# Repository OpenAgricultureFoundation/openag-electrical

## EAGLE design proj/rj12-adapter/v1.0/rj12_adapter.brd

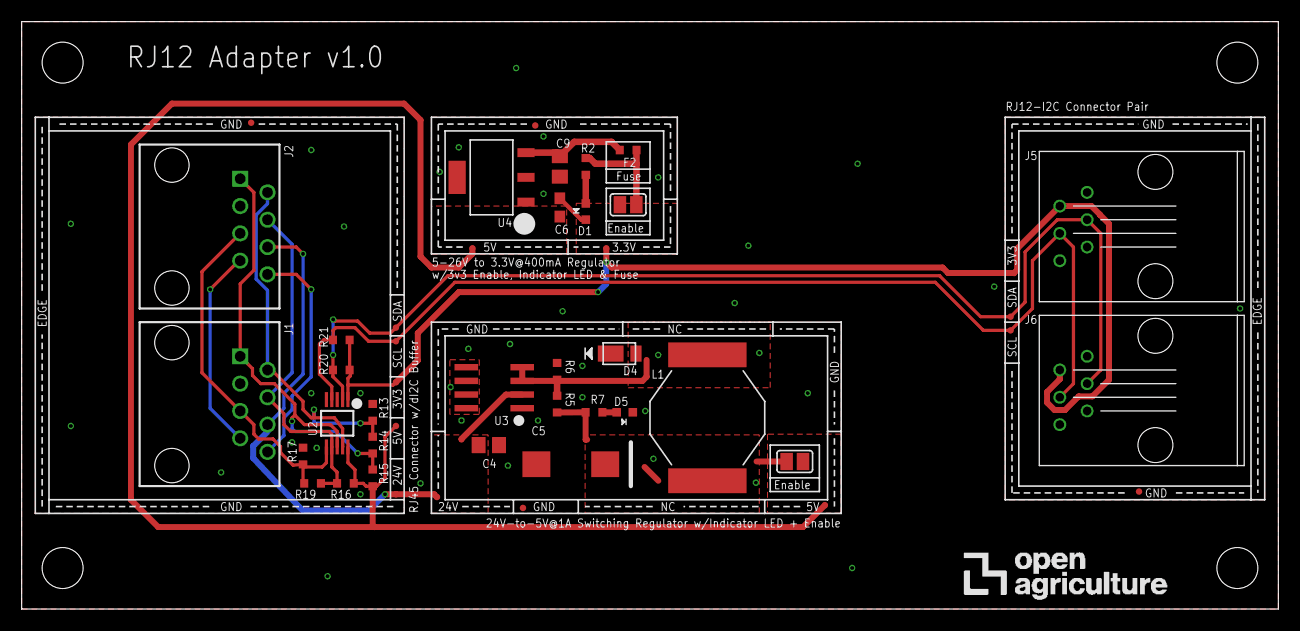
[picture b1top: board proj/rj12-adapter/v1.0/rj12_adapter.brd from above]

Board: 2 copper layers, 116.8 x 54.6 mm, 52 parts (1 on the bottom side), 18 nets.

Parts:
C4: 15uF; C0805
C5: 220uF; CT7343
C6: 0.1uF; C0603
C9: 10uF; C0805
D1, D5: APT1608; CHIPLED_0603
D4: SBR2A40P1-7; POWERDI123
F2: 400mA; 0603
FRAME1: DOCFIELD
J1, J2: 54602-908LF; OPENAG-V1-RJ45
J5, J6: OPENAG-I2C-RJ12
L1: 68uH; UP2B
R2, R7: 100; RC0603N
R5: 3.01K; RC0603N
R6: 976 Ohm; RC0603N
R13, R15, R16, R17: 600; RC0603N
R14, R19: 120; RC0603N
R20, R21: 10K; RC0603N
SJ2, SJ3: SOLDERJUMPER_REFLOW_NOPASTE
TP4, TP5, TP6, TP7, TP8, TP9, TP11, TP12, TP13, TP14, TP29, TP30, TP32, TP33, TP34, TP35: TPTP06R; TP06R
U2: PCA9615; SOP50P490X110-10N
U3: MIC4680; SOIC8
U4: LM2937; MP04A
U$1, U$2, U$3, U$4: OPENAG-CORNER-MOUNTING-HOLE
U$5: OPENAG-LOGO-750-MIL

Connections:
+3V3: J5.5, J6.5, R20.2, R21.2, SJ3.2, TP11.TP, TP30.TP, TP32.TP, U2.1
+5V: C6.1, R15.1, R16.2, SJ2.2, TP5.TP, TP29.TP, TP34.TP, U2.10, U4.1
+24V: C4.1, J1.24V(6), J2.24V(6), TP7.TP, TP35.TP, U3.2
DSCLM: J1.DSCLM(5), J2.DSCLM(5), R17.2, R19.1, U2.6
DSCLP: J1.DSCLP(4), J2.DSCLP(4), R16.1, R19.2, U2.7
DSDAM: J1.DSDAM(2), J2.DSDAM(2), R13.1, R14.2, U2.9
DSDAP: J1.DSDAP(1), J2.DSDAP(1), R14.1, R15.2, U2.8
GND: C4.2, C5.-, C6.2, C9.2, D1.C, D4.-, D5.C, J1.GND(3), J2.GND(3), J5.1, J6.1, R6.1, R13.2, R17.1, TP4.TP, TP6.TP, TP13.TP, TP33.TP, U2.5, U3.1, U3.5, U3.6, U3.7, U3.8, U4.2, U4.4
unnamed: D1.A, R2.1
unnamed: C9.1, F2.1, U4.3
unnamed: D4.+, L1.1, R5.1, R6.2, U3.3, U3.4
unnamed: D5.A, R7.1
unnamed: C5.+, L1.2, R5.2, R7.2, SJ2.1
REG_3V3_400MA: F2.2, R2.2, SJ3.1
SCL: J5.3, J6.3, R21.1, TP8.TP, TP12.TP, U2.4
SDA: J5.4, J6.4, R20.1, TP9.TP, TP14.TP, U2.2
USBM: J1.USBM(8), J2.USBM(8)
USBP: J1.USBP(7), J2.USBP(7)

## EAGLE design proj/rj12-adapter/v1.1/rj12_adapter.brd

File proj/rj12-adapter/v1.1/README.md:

# RJ12 to RJ45 Adapter v1.1
Enables devices on RJ12-I2C comm
system to interface with RJ45-dI2C-USB
comm system. Converts 24V & dI2C on 
RJ45 to 3V3 & I2C on RJ12.

### Contents
1. [Schematic](#schematic)
2. [Board Top](#board-top)
3. [Board Bottom](#board-bottom)
4. [Bill of Materials](rj12_adapter.csv)
5. [Gerber Files](rj12_adapter_v_1_1.zip)

### Schematic

### Board Top

### Board Bottom

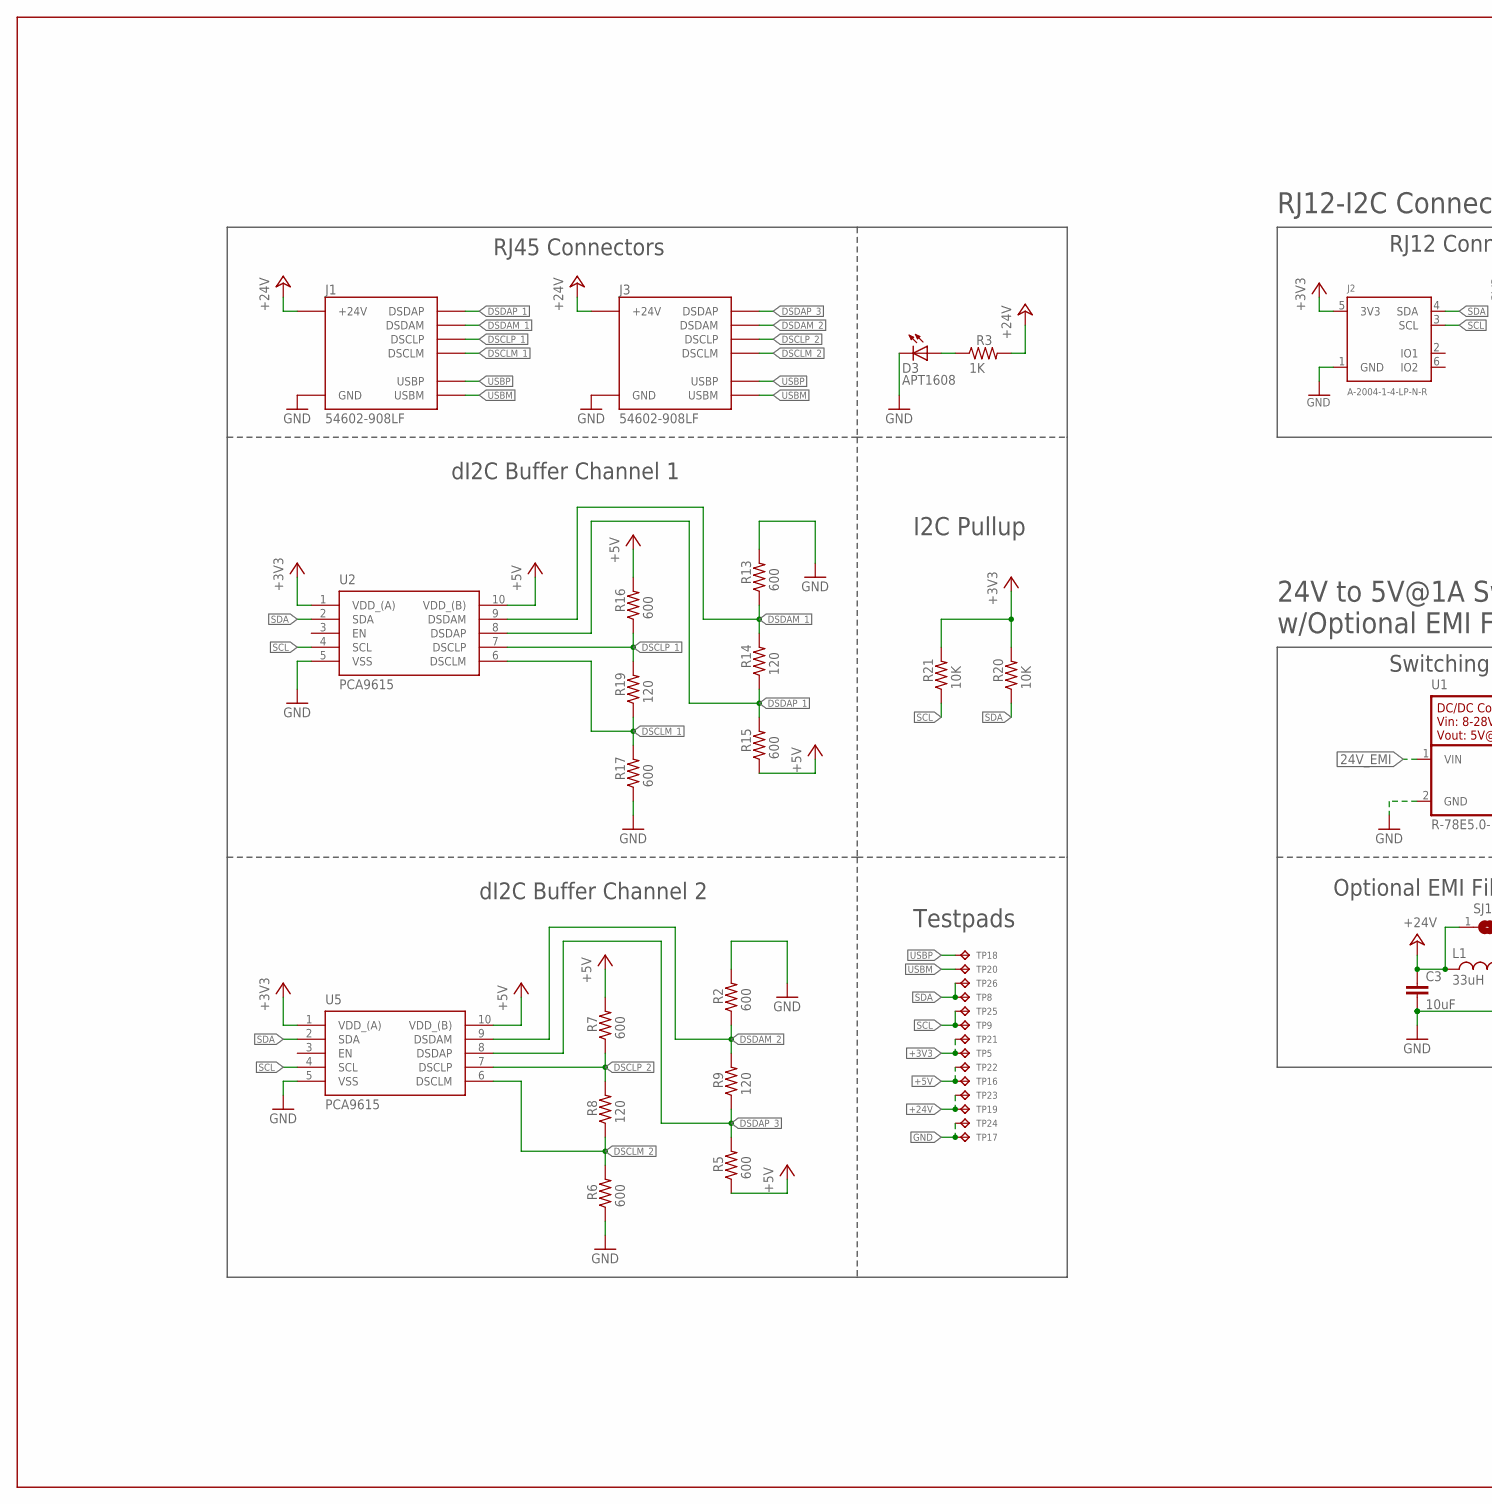
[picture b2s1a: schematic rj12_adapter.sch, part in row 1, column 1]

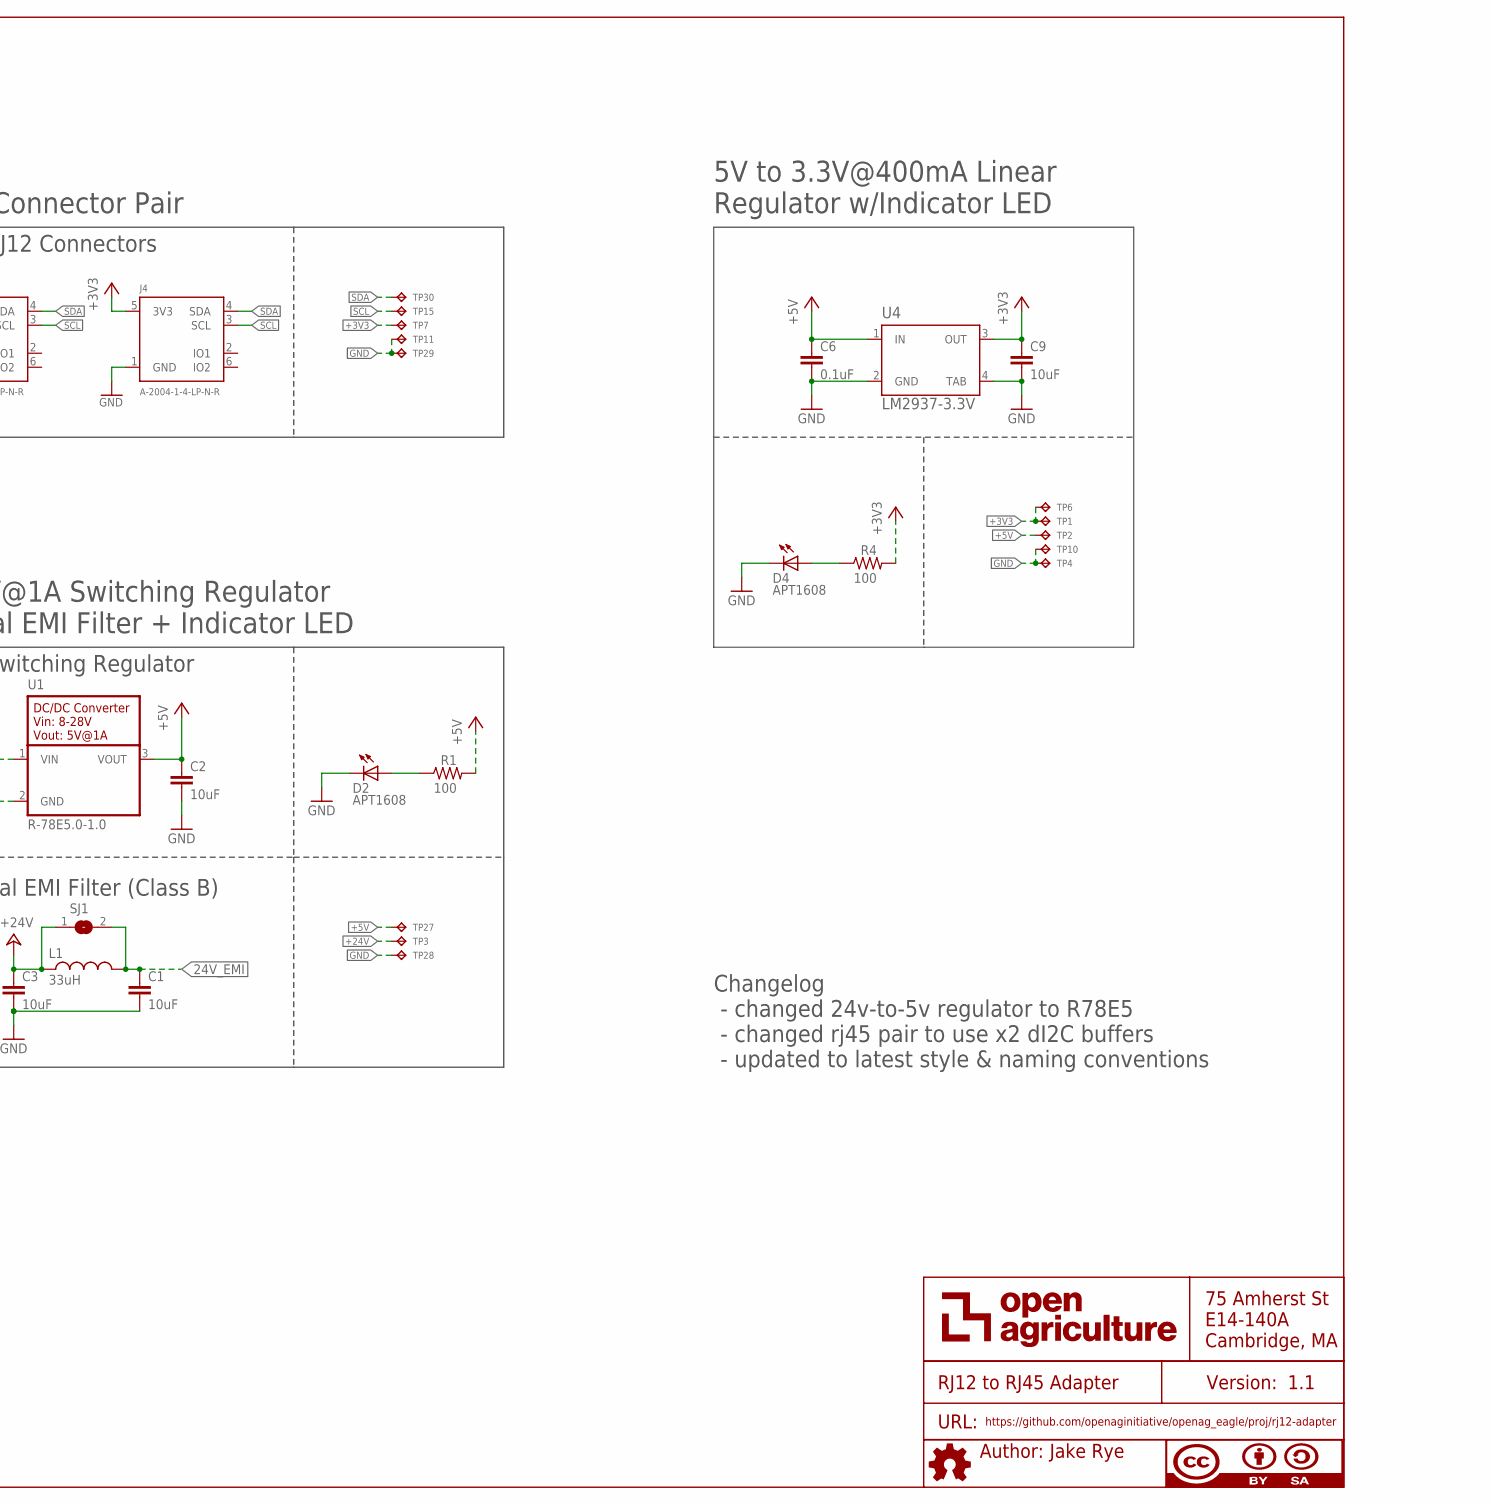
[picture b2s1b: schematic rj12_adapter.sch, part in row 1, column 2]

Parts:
C1, C2, C3, C9: 10uF; C0805
C6: 0.1uF; C0603
D2, D3, D4: APT1608; CHIPLED_0603
J1, J3: 54602-908LF; RJ45-DI2C-USB-54602-908LF
J2, J4: A-2004-1-4-LP-N-R; RJ12-I2C-A-2004-1-4-LP-N-R
L1: 33uH; 29333C
R1, R4: 100; RC0603N
R2, R5, R6, R7, R13, R15, R16, R17: 600; RC0603N
R3: 1K; RC0603N
R8, R9, R14, R19: 120; RC0603N
R20, R21: 10K; RC0603N
SJ1: SOLDERJUMPERREFLOW_NOPASTE; SJ1
TP1, TP2, TP4, TP5, TP6, TP7, TP8, TP9, TP10, TP11, TP15, TP16, TP17, TP18, TP19, TP20, TP21, TP22, TP23, TP24, TP25, TP26, TP29, TP30: TPTP04R; TP04R
TP3, TP27, TP28: TPTP06R; TP06R
U1: R-78E5.0-1.0
U2, U5: PCA9615; SOP50P490X110-10N
U4: LM2937-3.3V; MP04A
U$6: AUTHOR
U$7: TITLE

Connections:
24V_EMI: C1.1, L1.2, SJ1.2, U1.1 (VIN)
+3V3: C9.1, J2.5 (3V3), J4.5 (3V3), R4.2, R20.2, R21.2, TP1.1, TP5.1, TP6.1, TP7.1, TP21.1, U2.1 (VDD_(A)), U4.3 (OUT), U5.1 (VDD_(A))
+5V: C2.1, C6.1, R1.2, R5.1, R7.2, R15.1, R16.2, TP2.1, TP16.1, TP22.1, TP27.TP, U1.3 (VOUT), U2.10 (VDD_(B)), U4.1 (IN), U5.10 (VDD_(B))
+24V: C3.1, J1.24V(6) (+24V), J3.24V(6) (+24V), L1.1, R3.2, SJ1.1, TP3.TP, TP19.1, TP23.1
DSCLM_1: J1.DSCLM(5) (DSCLM), R17.2, R19.1, U2.6 (DSCLM)
DSCLM_2: J3.DSCLM(5) (DSCLM), R6.2, R8.1, U5.6 (DSCLM)
DSCLP_1: J1.DSCLP(4) (DSCLP), R16.1, R19.2, U2.7 (DSCLP)
DSCLP_2: J3.DSCLP(4) (DSCLP), R7.1, R8.2, U5.7 (DSCLP)
DSDAM_1: J1.DSDAM(2) (DSDAM), R13.1, R14.2, U2.9 (DSDAM)
DSDAM_2: J3.DSDAM(2) (DSDAM), R2.1, R9.2, U5.9 (DSDAM)
DSDAP_1: J1.DSDAP(1) (DSDAP), R14.1, R15.2, U2.8 (DSDAP)
DSDAP_3: J3.DSDAP(1) (DSDAP), R5.2, R9.1, U5.8 (DSDAP)
GND: C1.2, C2.2, C3.2, C6.2, C9.2, D2.C, D3.C, D4.C, J1.GND(3) (GND), J2.1 (GND), J3.GND(3) (GND), J4.1 (GND), R2.2, R6.1, R13.2, R17.1, TP4.1, TP10.1, TP11.1, TP17.1, TP24.1, TP28.TP, TP29.1, U1.2 (GND), U2.5 (VSS), U4.2 (GND), U4.4 (TAB), U5.5 (VSS)
unnamed: D4.A, R4.1
unnamed: D2.A, R1.1
unnamed: D3.A, R3.1
SCL: J2.3 (SCL), J4.3 (SCL), R21.1, TP9.1, TP15.1, TP25.1, U2.4 (SCL), U5.4 (SCL)
SDA: J2.4 (SDA), J4.4 (SDA), R20.1, TP8.1, TP26.1, TP30.1, U2.2 (SDA), U5.2 (SDA)
USBM: J1.USBM(8) (USBM), J3.USBM(8) (USBM), TP20.1
USBP: J1.USBP(7) (USBP), J3.USBP(7) (USBP), TP18.1

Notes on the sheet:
5V to 3.3V@400mA Linear Regulator w/Indicator LED
dI2C Buffer Channel 1
RJ45 Connectors
RJ12-I2C Connector Pair
24V to 5V@1A Switching Regulator w/Optional EMI Filter + Indicator LED
Switching Regulator
Optional EMI Filter (Class B)
dI2C Buffer Channel 2
Testpads
I2C Pullup
RJ12 Connectors
Changelog - changed 24v-to-5v regulator to R78E5 - changed rj45 pair to use x2 dI2C buffers - updated to latest style & naming conventions

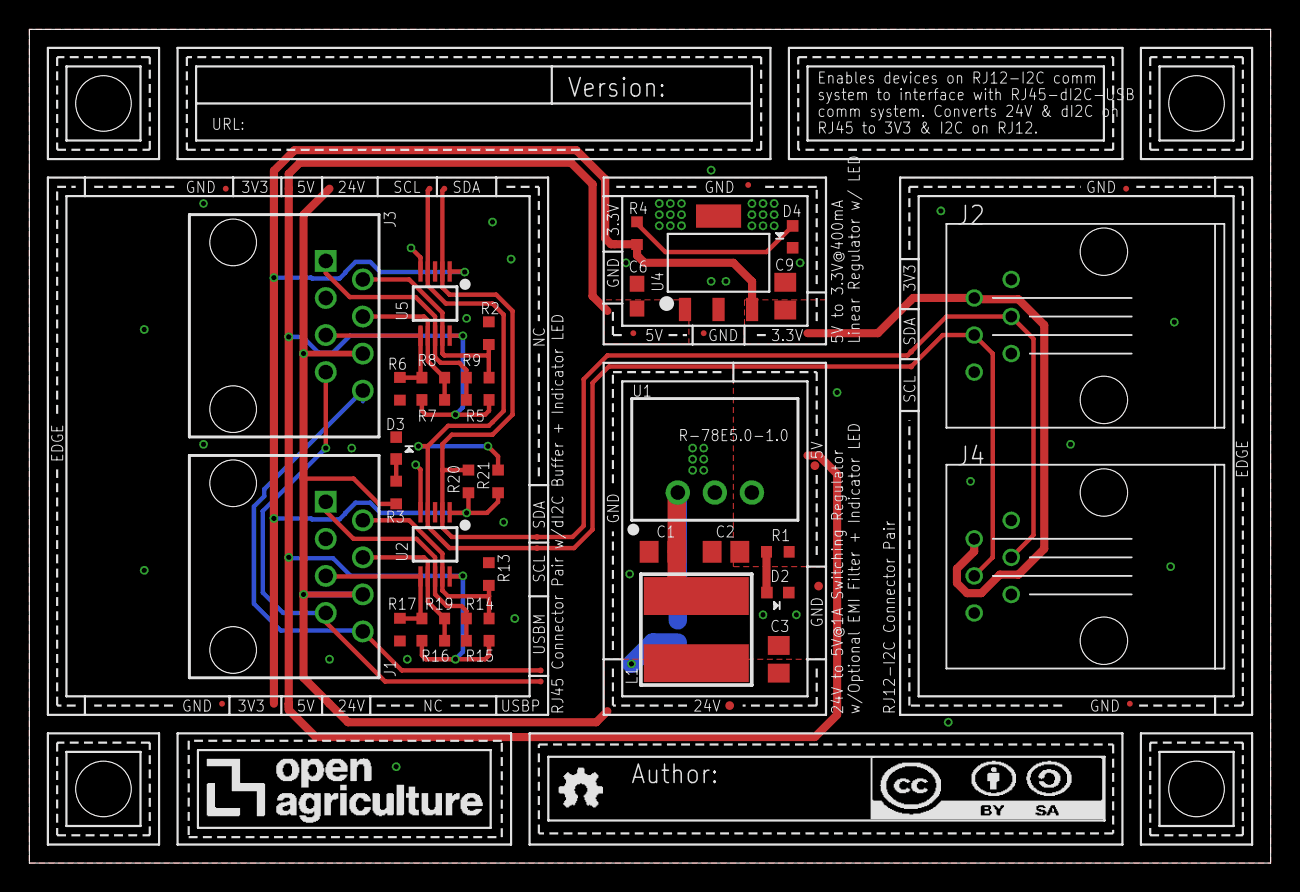
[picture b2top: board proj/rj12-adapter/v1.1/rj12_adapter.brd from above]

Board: 2 copper layers, 85.1 x 57.1 mm, 70 parts (1 on the bottom side), 20 nets.

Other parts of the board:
U$1, U$2, U$3, U$4: CORNER
U$5: LOGO
U$9: CAMBRIDGE-MAP-RJ12-ADAPTER-V-1-1

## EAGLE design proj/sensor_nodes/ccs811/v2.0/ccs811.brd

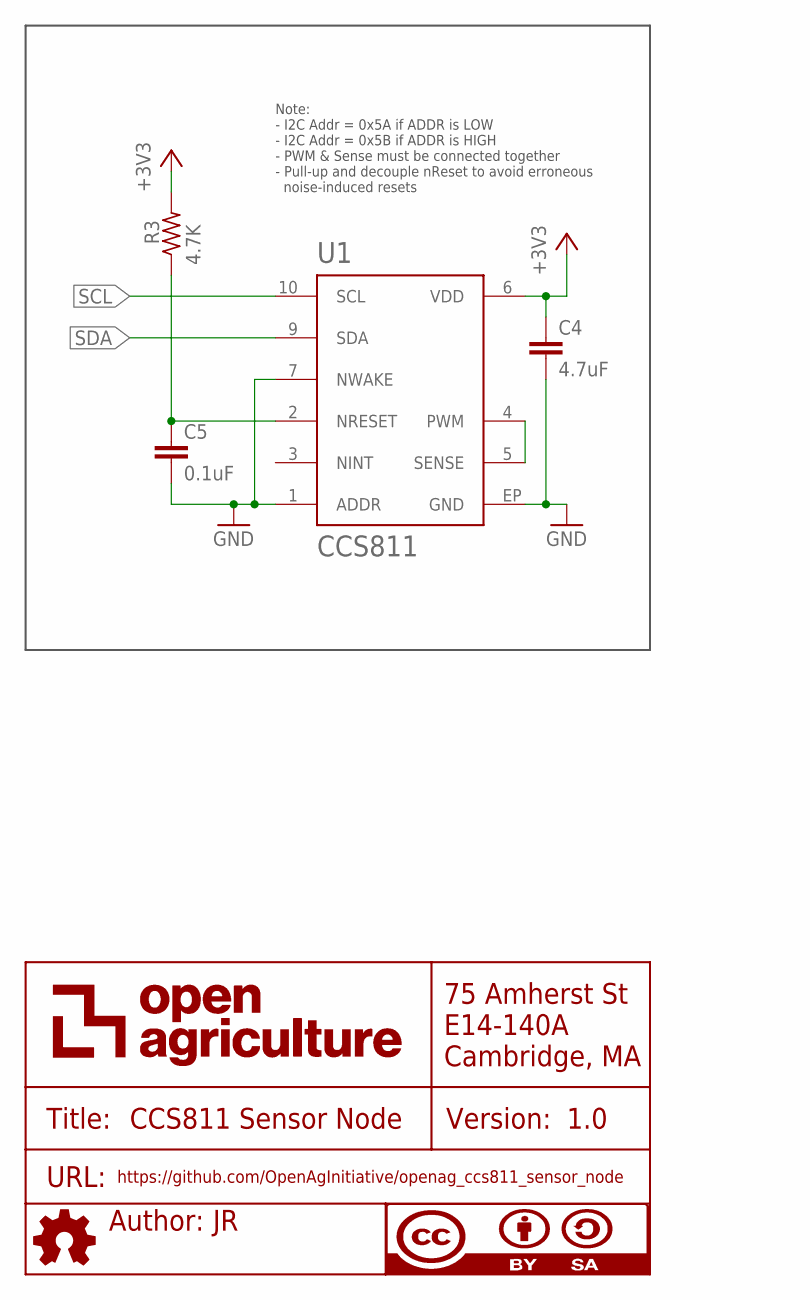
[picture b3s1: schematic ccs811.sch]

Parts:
C4: 4.7uF; C0805
C5: 0.1uF; C0603
FRAME1: DOCFIELD
R3: 4.7K; R1206
U1: CCS811

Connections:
+3V3: C4.1, R3.2, U1.6 (VDD)
GND: C4.2, C5.2, U1.1 (ADDR), U1.7 (NWAKE), U1.EP (GND)
unnamed: U1.4 (PWM), U1.5 (SENSE)
unnamed: C5.1, R3.1, U1.2 (NRESET)
SCL: U1.10 (SCL)
SDA: U1.9 (SDA)

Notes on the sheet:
Note: - I2C Addr = 0x5A if ADDR is LOW - I2C Addr = 0x5B if ADDR is HIGH - PWM & Sense must be connected together - Pull-up and decouple nReset to avoid erroneous noise-induced resets

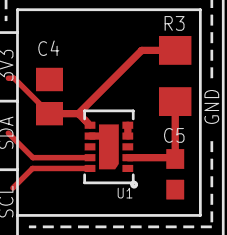
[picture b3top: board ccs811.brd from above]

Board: 2 copper layers, 6 parts (1 on the bottom side), 4 nets.

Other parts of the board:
U$1: OPENAG-LOGO-750-MIL
